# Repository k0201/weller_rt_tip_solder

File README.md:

# weller_rt_tip_solder
Weller tip hand solder on stm32

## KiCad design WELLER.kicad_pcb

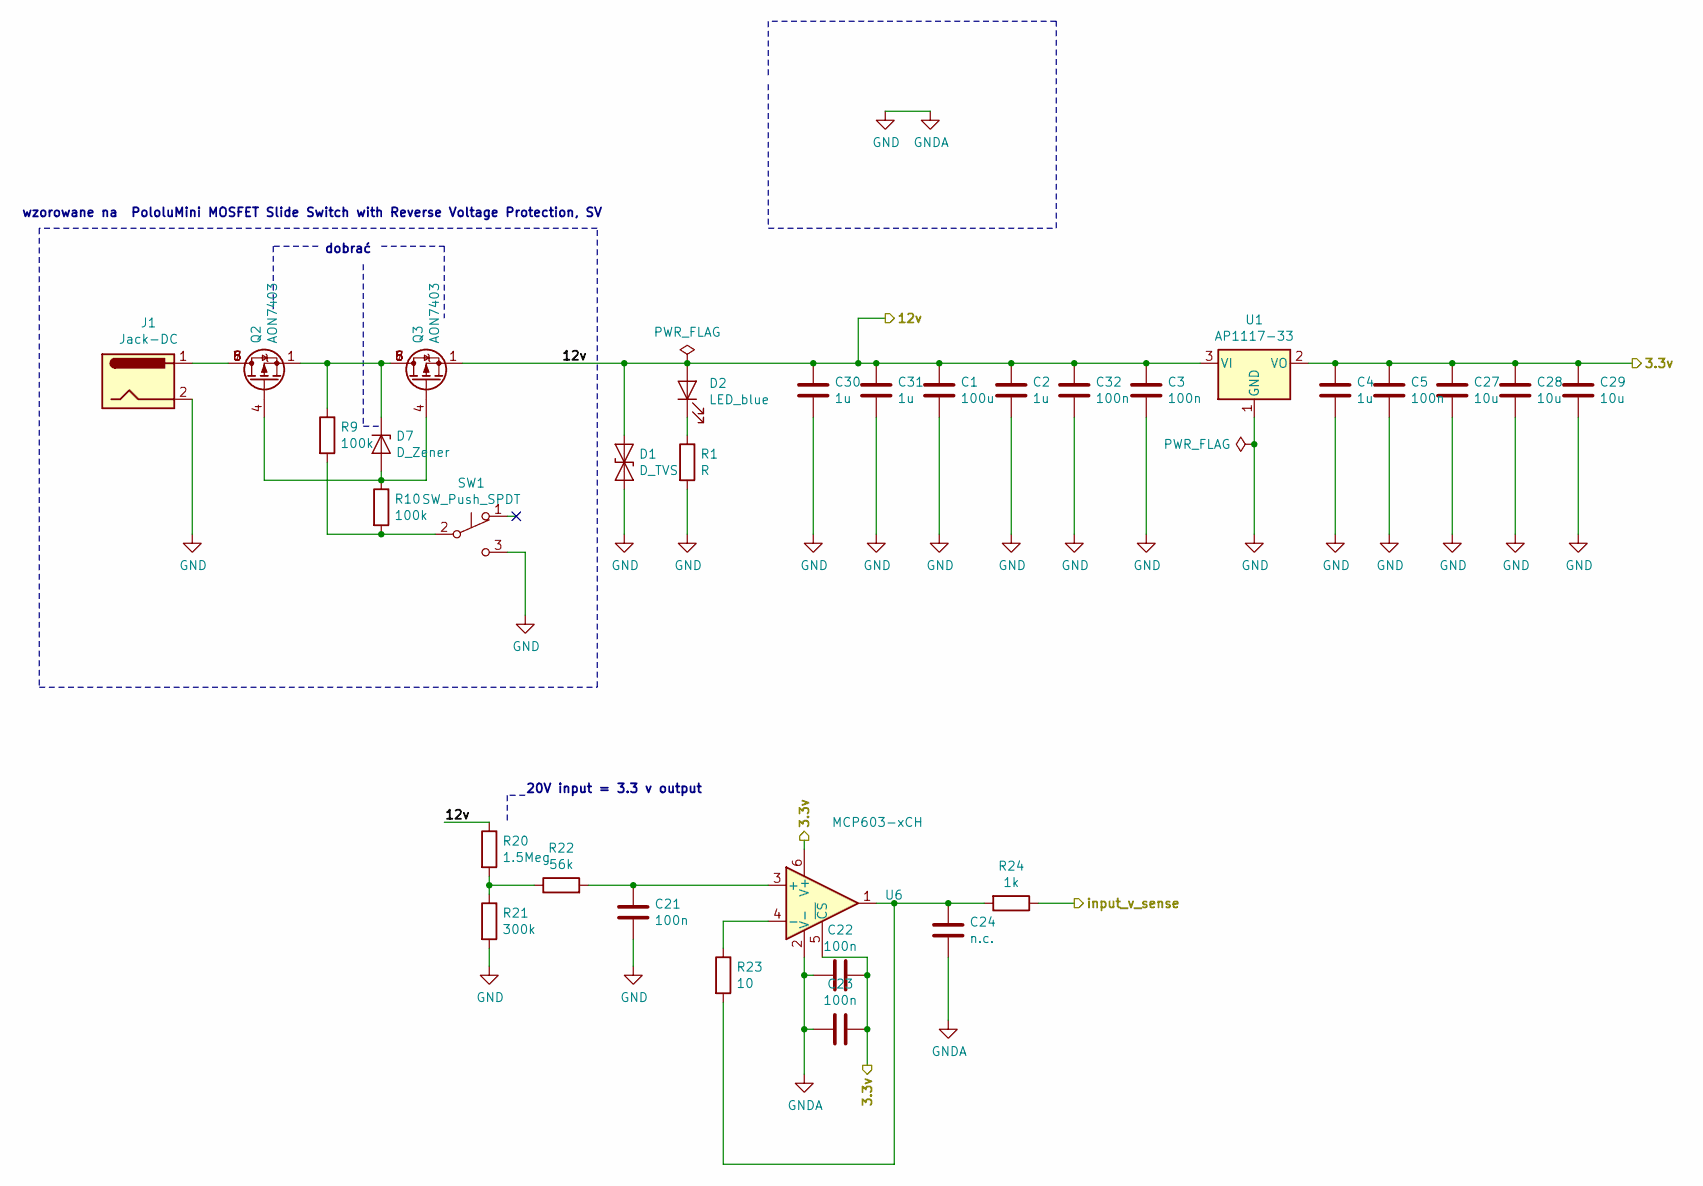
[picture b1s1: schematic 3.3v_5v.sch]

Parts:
C1: 100u; CP_EIA-3216-10_Kemet-I
C2, C4, C30, C31: 1u; C_0805_2012Metric
C3, C5, C21, C22, C32: 100n; C_0603_1608Metric_Pad1.05x0.95mm_HandSolder
C23: 100n; C_0805_2012Metric
C24: n.c.; C_0603_1608Metric
C27, C28, C29: 10u; C_0805_2012Metric
D1: D_TVS; D_SMA-SMB_Universal_Handsoldering
D2: LED_blue; LED_0603_1608Metric
D7: D_Zener; D_0805_2012Metric_Castellated
J1: Jack-DC; jackDC_cutout
Q2, Q3: AON7403; DFN_3X3_EP
R1: R; R_0603_1608Metric
R9, R10: 100k; R_0603_1608Metric
R20: 1.5Meg; R_0603_1608Metric_Pad1.05x0.95mm_HandSolder
R21: 300k; R_0603_1608Metric_Pad1.05x0.95mm_HandSolder
R22: 56k; R_0603_1608Metric
R23: 10; R_0603_1608Metric
R24: 1k; R_0603_1608Metric
SW1: SW_Push_SPDT; SW_SPDT_CK-JS102011SAQN
U1: AP1117-33; SOT-223-3_TabPin2
U6: MCP603-xCH; SOT-23-6

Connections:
/stm32/input_sense: R24.1; also elsewhere on the board
/tip_driving/3.3V_analog: C4.1, C5.1, C22.2, C23.2, C27.1, C28.1, C29.1, U1.2 (VO), U6.5 (~CS), U6.6 (V+); also elsewhere on the board
/tip_driving/12V: C1.1, C2.1, C3.1, C30.1, C31.1, C32.1, D1.2 (A2), D2.2 (A), Q3.1 (S), Q3.2 (S), Q3.3 (S), R20.1, U1.3 (VI); also elsewhere on the board
GND: C1.2, C2.2, C3.2, C4.2, C5.2, C21.2, C22.1, C23.1, C24.2, C27.2, C28.2, C29.2, C30.2, C31.2, C32.2, D1.1 (A1), J1.2, R1.2, R21.2, SW1.3 (C), U1.1 (GND), U6.2 (V-); also elsewhere on the board
unnamed: C21.1, R22.2, U6.3 (+)
unnamed: C24.1, R23.2, R24.2, U6.1
unnamed: D2.1 (K), R1.1
unnamed: D7.1 (K), Q2.1 (S), Q2.2 (S), Q2.3 (S), Q3.5 (D), Q3.6 (D), Q3.7 (D), Q3.8 (D), R9.1
unnamed: D7.2 (A), Q2.4 (G), Q3.4 (G), R10.1
unnamed: J1.1, Q2.5 (D), Q2.6 (D), Q2.7 (D), Q2.8 (D)
unnamed: R9.2, R10.2, SW1.2 (B)
unnamed: R20.2, R21.1, R22.1
unnamed: R23.1, U6.4 (-)

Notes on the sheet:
20V input = 3.3 v output
dobrać
wzorowane na PololuMini MOSFET Slide Switch with Reverse Voltage Protection, SV

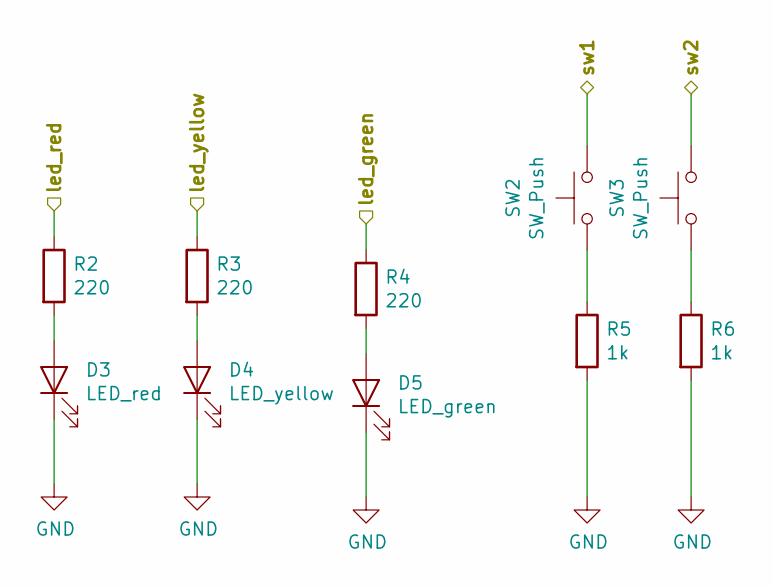
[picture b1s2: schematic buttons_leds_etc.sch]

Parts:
D3: LED_red; LED_0603_1608Metric
D4: LED_yellow; LED_0603_1608Metric
D5: LED_green; LED_0603_1608Metric
R2, R3, R4: 220; R_0603_1608Metric
R5, R6: 1k; R_0603_1608Metric
SW2, SW3: SW_Push; SW_SPST_B3U-3000P

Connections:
/but_led/sw1: SW2.2; also elsewhere on the board
/but_led/sw2: SW3.2; also elsewhere on the board
/stm32/led_g: R4.1; also elsewhere on the board
/stm32/led_r: R2.1; also elsewhere on the board
/stm32/led_y: R3.1; also elsewhere on the board
GND: D3.1 (K), D4.1 (K), D5.1 (K), R5.2, R6.2; also elsewhere on the board
unnamed: D3.2 (A), R2.2
unnamed: D4.2 (A), R3.2
unnamed: D5.2 (A), R4.2
unnamed: R5.1, SW2.1
unnamed: R6.1, SW3.1

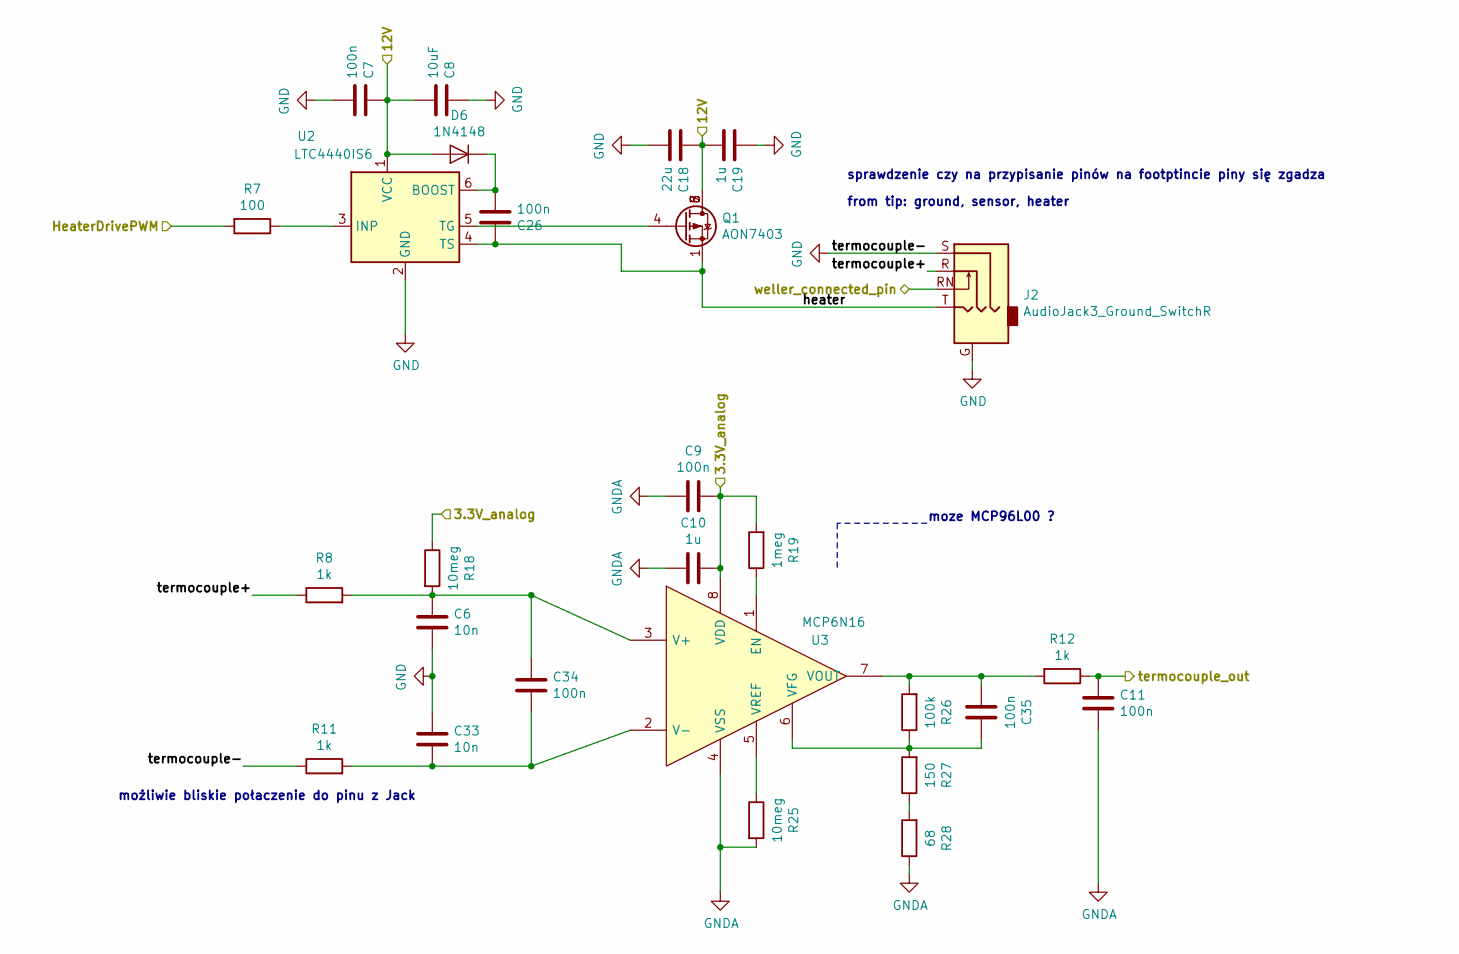
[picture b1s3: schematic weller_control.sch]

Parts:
C6, C33: 10n; C_0603_1608Metric_Pad1.05x0.95mm_HandSolder
C7, C9, C26, C34, C35: 100n; C_0603_1608Metric_Pad1.05x0.95mm_HandSolder
C8: 10uF; C_0805_2012Metric
C10, C19: 1u; C_0805_2012Metric
C11: 100n; C_0603_1608Metric
C18: 22u; CP_EIA-2012-12_Kemet-R
D6: 1N4148; D_0805_2012Metric
J2: AudioJack3_Ground_SwitchR; Jack Audio150320cutout
Q1: AON7403; DFN_3X3_EP
R7: 100; R_1206_3216Metric
R8, R11, R12: 1k; R_0603_1608Metric
R18, R25: 10meg; R_0603_1608Metric
R19: 1meg; R_0603_1608Metric
R26: 100k; R_0603_1608Metric
R27: 150; R_0603_1608Metric
R28: 68; R_0603_1608Metric
U2: LTC4440IS6; SOT-23-6
U3: MCP6N16; MSOP-8_3x3mm_P0.65mm; Manufacturer_Part_Number MCP6n16-100E/MS; Mouser Part Number 579-MCP6N16-100E/MS

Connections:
/stm32/termocouple: C11.1, R12.1; also elsewhere on the board
/stm32/weller_con1: J2.RN; also elsewhere on the board
/tip_driving/3.3V_analog: C9.2, C10.2, R18.1, R19.2, U3.8 (VDD); also elsewhere on the board
/tip_driving/12V: C7.1, C8.2, C18.1, C19.2, D6.2 (A), Q1.5 (D), Q1.6 (D), Q1.7 (D), Q1.8 (D), U2.1 (VCC); also elsewhere on the board
/tip_driving/HeaterDrivePWM: R7.2; also elsewhere on the board
/tip_driving/heater: C26.1, J2.T, Q1.1 (S), Q1.2 (S), Q1.3 (S), U2.4 (TS)
/tip_driving/termocouple+: J2.R, R8.1
GND: C6.2, C7.2, C8.1, C9.1, C10.1, C11.2, C18.2, C19.1, C33.1, J2.G, J2.S, R11.1, R25.2, R28.1, U2.2 (GND), U3.4 (VSS); also elsewhere on the board
unnamed: C26.2, D6.1 (K), U2.6 (BOOST)
unnamed: C33.2, C34.2, R11.2, U3.2 (V-)
unnamed: C6.1, C34.1, R8.2, R18.2, U3.3 (V+)
unnamed: C35.1, R12.2, R26.2, U3.7 (VOUT)
unnamed: C35.2, R26.1, R27.2, U3.6 (VFG)
unnamed: Q1.4 (G), U2.5 (TG)
unnamed: R7.1, U2.3 (INP)
unnamed: R19.1, U3.1 (EN)
unnamed: R25.1, U3.5 (VREF)
unnamed: R27.1, R28.2

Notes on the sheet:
sprawdzenie czy na przypisanie pinów na footptincie piny się zgadza
from tip: ground, sensor, heater
możliwie bliskie połaczenie do pinu z Jack
moze MCP96L00 ?

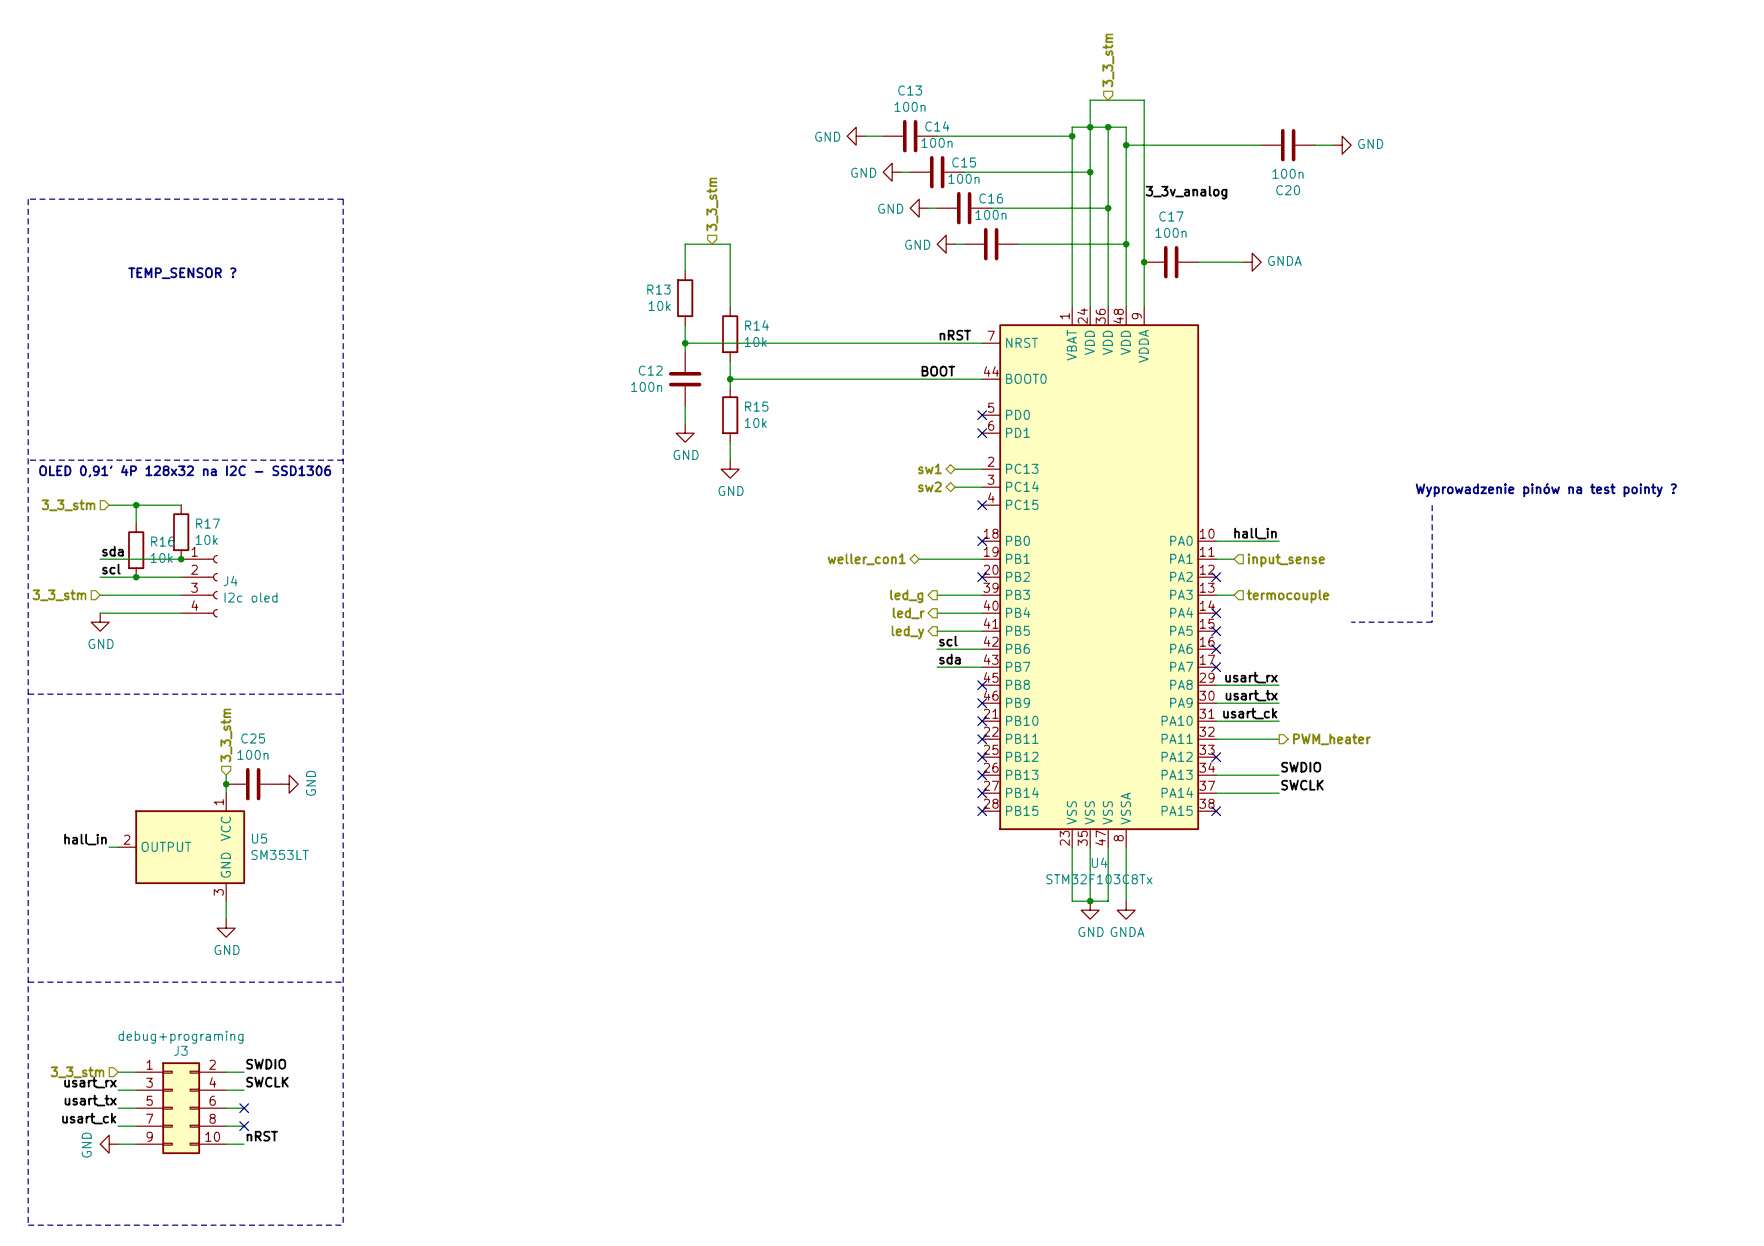
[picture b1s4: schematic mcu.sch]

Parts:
C12, C13, C14, C15, C16, C17, C20, C25: 100n; C_0603_1608Metric_Pad1.05x0.95mm_HandSolder
J3: debug+programing; PinHeader_2x05_P1.27mm_Vertical_SMD
J4: I2c oled; PinHeader_1x04_P2.54mm_Vertical
R13, R14, R15, R16, R17: 10k; R_0603_1608Metric
U4: STM32F103C8Tx; LQFP-48_7x7mm_P0.5mm
U5: SM353LT; SOT-23

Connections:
/but_led/sw1: U4.2 (PC13); also elsewhere on the board
/but_led/sw2: U4.3 (PC14); also elsewhere on the board
/stm32/BOOT: R14.2, R15.1, U4.44 (BOOT0)
/stm32/SWCLK: J3.4, U4.37 (PA14)
/stm32/SWDIO: J3.2, U4.34 (PA13)
/stm32/hall_in: U4.10 (PA0), U5.2 (OUTPUT)
/stm32/input_sense: U4.11 (PA1); also elsewhere on the board
/stm32/led_g: U4.39 (PB3); also elsewhere on the board
/stm32/led_r: U4.40 (PB4); also elsewhere on the board
/stm32/led_y: U4.41 (PB5); also elsewhere on the board
/stm32/nRST: C12.2, J3.10, R13.1, U4.7 (NRST)
/stm32/scl: J4.2, R16.2, U4.42 (PB6)
/stm32/sda: J4.1, R17.2, U4.43 (PB7)
/stm32/termocouple: U4.13 (PA3); also elsewhere on the board
/stm32/usart_ck: J3.7, U4.31 (PA10)
/stm32/usart_rx: J3.3, U4.29 (PA8)
/stm32/usart_tx: J3.5, U4.30 (PA9)
/stm32/weller_con1: U4.19 (PB1); also elsewhere on the board
/tip_driving/3.3V_analog: C13.1, C14.1, C15.1, C16.1, C17.2, C20.1, C25.2, J3.1, J4.3, R13.2, R14.1, R16.1, R17.1, U4.1 (VBAT), U4.9 (VDDA), U4.24 (VDD), U4.36 (VDD), U4.48 (VDD), U5.1 (VCC); also elsewhere on the board
/tip_driving/HeaterDrivePWM: U4.32 (PA11); also elsewhere on the board
GND: C12.1, C13.2, C14.2, C15.2, C16.2, C17.1, C20.2, C25.1, J3.9, J4.4, R15.2, U4.8 (VSSA), U4.23 (VSS), U4.35 (VSS), U4.47 (VSS), U5.3 (GND); also elsewhere on the board

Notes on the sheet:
OLED 0,91' 4P 128x32 na I2C - SSD1306
TEMP_SENSOR ?
Wyprowadzenie pinów na test pointy ?

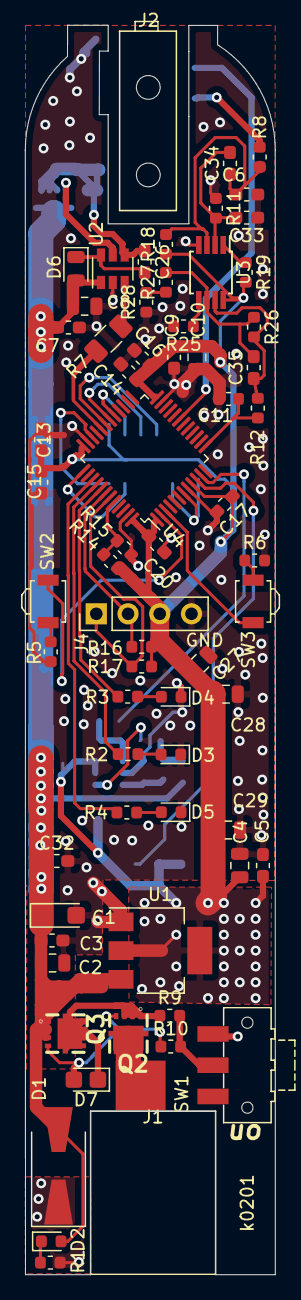
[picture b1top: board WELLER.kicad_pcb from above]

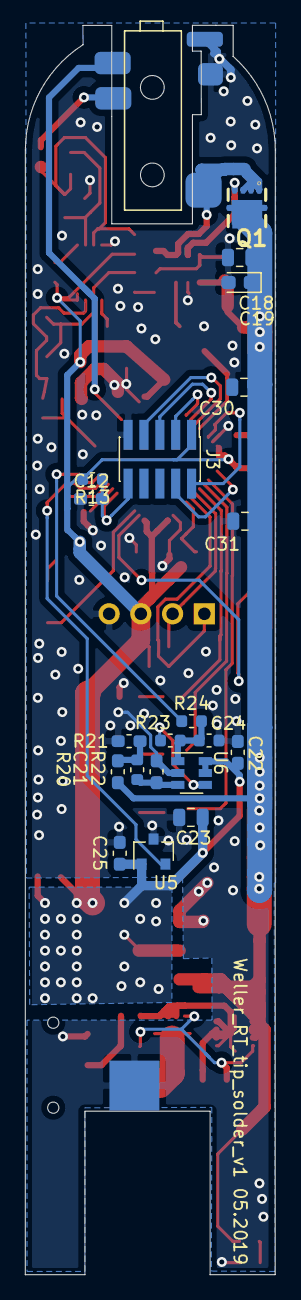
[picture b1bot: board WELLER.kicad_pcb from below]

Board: 2 copper layers, 20.0 x 100.0 mm, 86 parts (20 on the bottom side), 48 nets.

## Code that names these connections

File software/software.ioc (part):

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Mcu.Name=STM32F103C(8-B)Tx
Mcu.Package=LQFP48
Mcu.UserName=STM32F103C8Tx
PA0-WKUP.GPIOParameters=GPIO_Label
PA0-WKUP.GPIO_Label=hall
PA0-WKUP.Signal=ADCx_IN0
PA1.GPIOParameters=GPIO_Label
PA1.GPIO_Label=inputV
PA1.Signal=ADCx_IN1
PA10.Mode=Synchronous
PA10.Signal=USART1_RX
PA11.GPIOParameters=GPIO_Speed,GPIO_Label
PA11.GPIO_Label=pwm_heater
PA11.GPIO_Speed=GPIO_SPEED_FREQ_MEDIUM
PA11.Signal=S_TIM1_CH4
PA13.Mode=Serial_Wire
PA13.Signal=SYS_JTMS-SWDIO
PA14.Mode=Serial_Wire
PA14.Signal=SYS_JTCK-SWCLK
PA3.GPIOParameters=GPIO_Label
PA3.GPIO_Label=termocouple
PA3.Signal=ADCx_IN3
PA4.Signal=ADCx_IN4
PA8.Mode=Synchronous
PA8.Signal=USART1_CK
PA9.Mode=Synchronous
PA9.Signal=USART1_TX
PB1.Signal=ADCx_IN9
PB3.GPIOParameters=GPIO_PuPd,GPIO_Label
PB3.GPIO_Label=ledG
PB3.GPIO_PuPd=GPIO_NOPULL
PB3.Signal=GPIO_Output
PB4.GPIOParameters=GPIO_Label
PB4.GPIO_Label=ledR
PB4.Signal=GPIO_Output
PB5.GPIOParameters=GPIO_Label
PB5.GPIO_Label=ledY
PB5.Signal=GPIO_Output
PB6.Mode=I2C
PB6.Signal=I2C1_SCL
PB7.Mode=I2C
PB7.Signal=I2C1_SDA
PC13-TAMPER-RTC.GPIOParameters=GPIO_PuPd,GPIO_Label
PC13-TAMPER-RTC.GPIO_Label=sw1
PC13-TAMPER-RTC.GPIO_PuPd=GPIO_PULLUP
PC13-TAMPER-RTC.Signal=GPIO_Input
PC14-OSC32_IN.GPIOParameters=GPIO_PuPd,GPIO_Label
PC14-OSC32_IN.GPIO_Label=sw2
PC14-OSC32_IN.GPIO_PuPd=GPIO_PULLUP
PC14-OSC32_IN.Signal=GPIO_Input
PD0-OSC_IN.GPIOParameters=GPIO_Label
PD0-OSC_IN.GPIO_Label=weller_connnected?
PD0-OSC_IN.Signal=GPIO_Input
RCC.SYSCLKFreq_VALUE=44000000
RCC.SYSCLKSource=RCC_SYSCLKSOURCE_PLLCLK
board=custom

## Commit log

2019-04-17 Add files via upload
    first commit not schmatic done
2019-05-27 duży update, gotowe pcb
2019-05-27 dodanie pullup do i2c i screenow
2019-05-29 poprawki na sch
2019-05-29 duży update, drc przechodzi
2019-05-29 dodanie pinoutu z cuba
2019-06-16 dodanie pomiaru napięcia zasilającego grzałkę
2019-06-22 poprawki głownie na pcb zaokrąglenie strony z grotem
2019-06-24 wyciecie przy gnieździe jack - dodanie 3d gniazda, update jpg
2019-06-26 dodanie pdf schematów
2019-07-04 zmiana tranzystora
2019-07-09 update front endu do termopary i przełącznika zasilającego
2020-01-22 update błędnego podpięcia pmosa na wejściu do układu, oras software testujący oled, przyciski i ledy
